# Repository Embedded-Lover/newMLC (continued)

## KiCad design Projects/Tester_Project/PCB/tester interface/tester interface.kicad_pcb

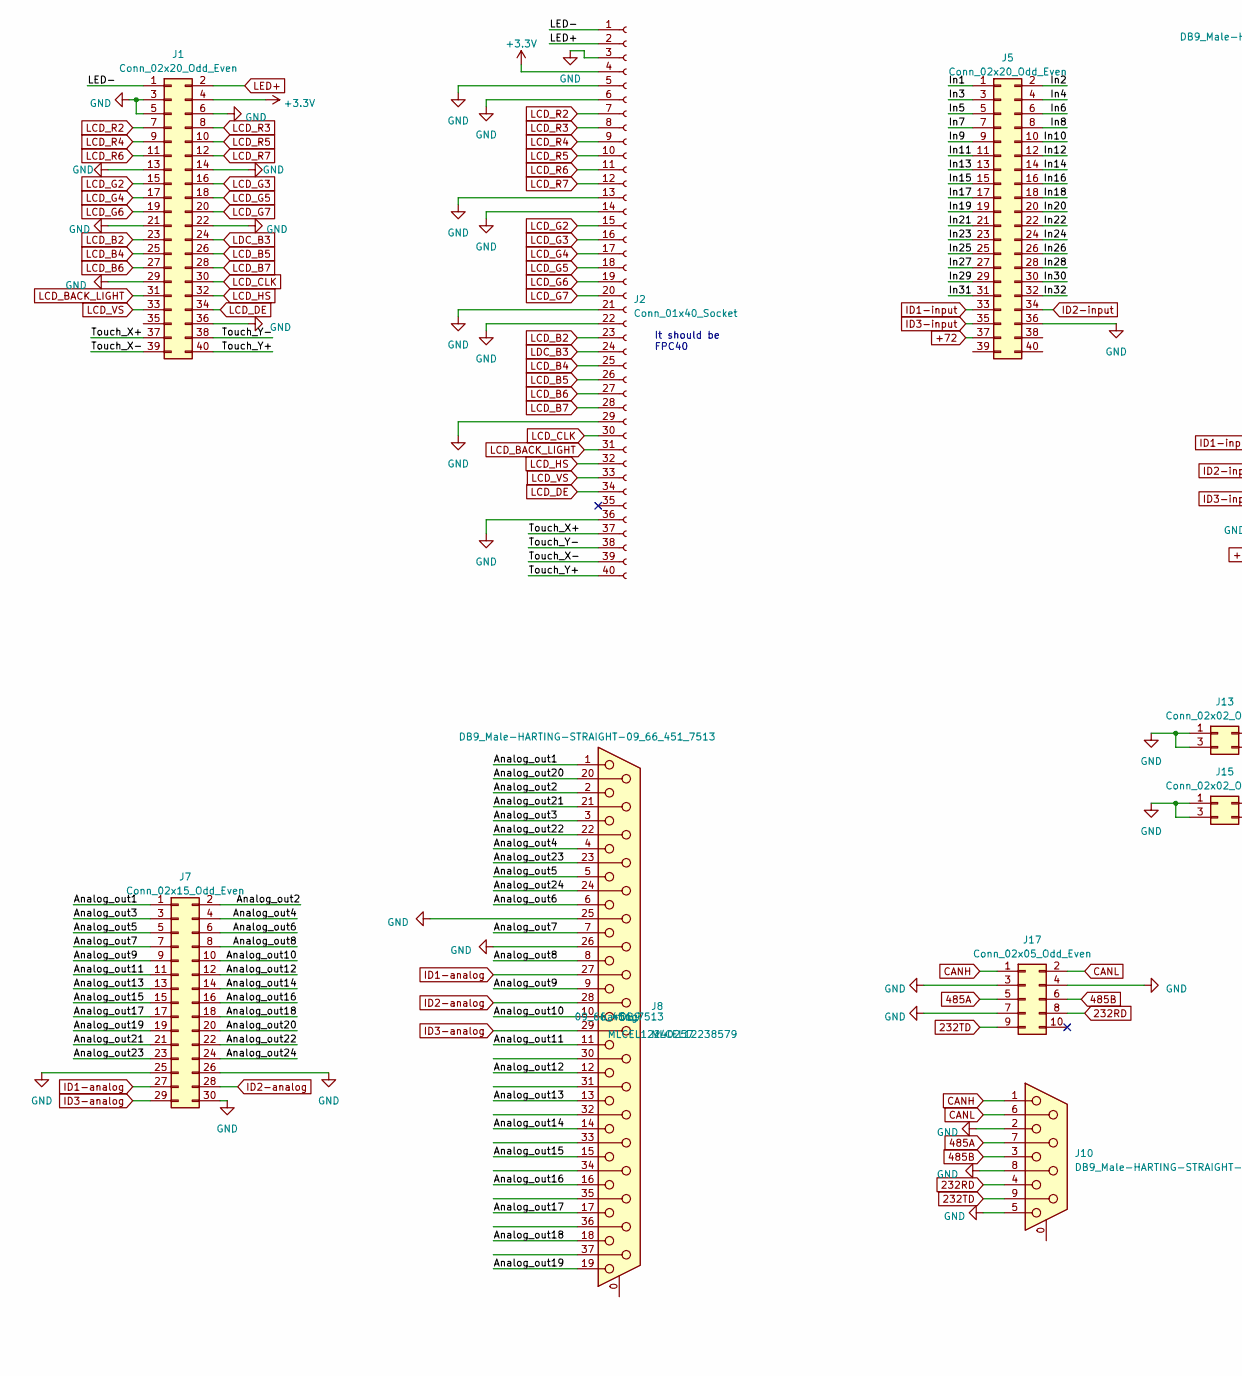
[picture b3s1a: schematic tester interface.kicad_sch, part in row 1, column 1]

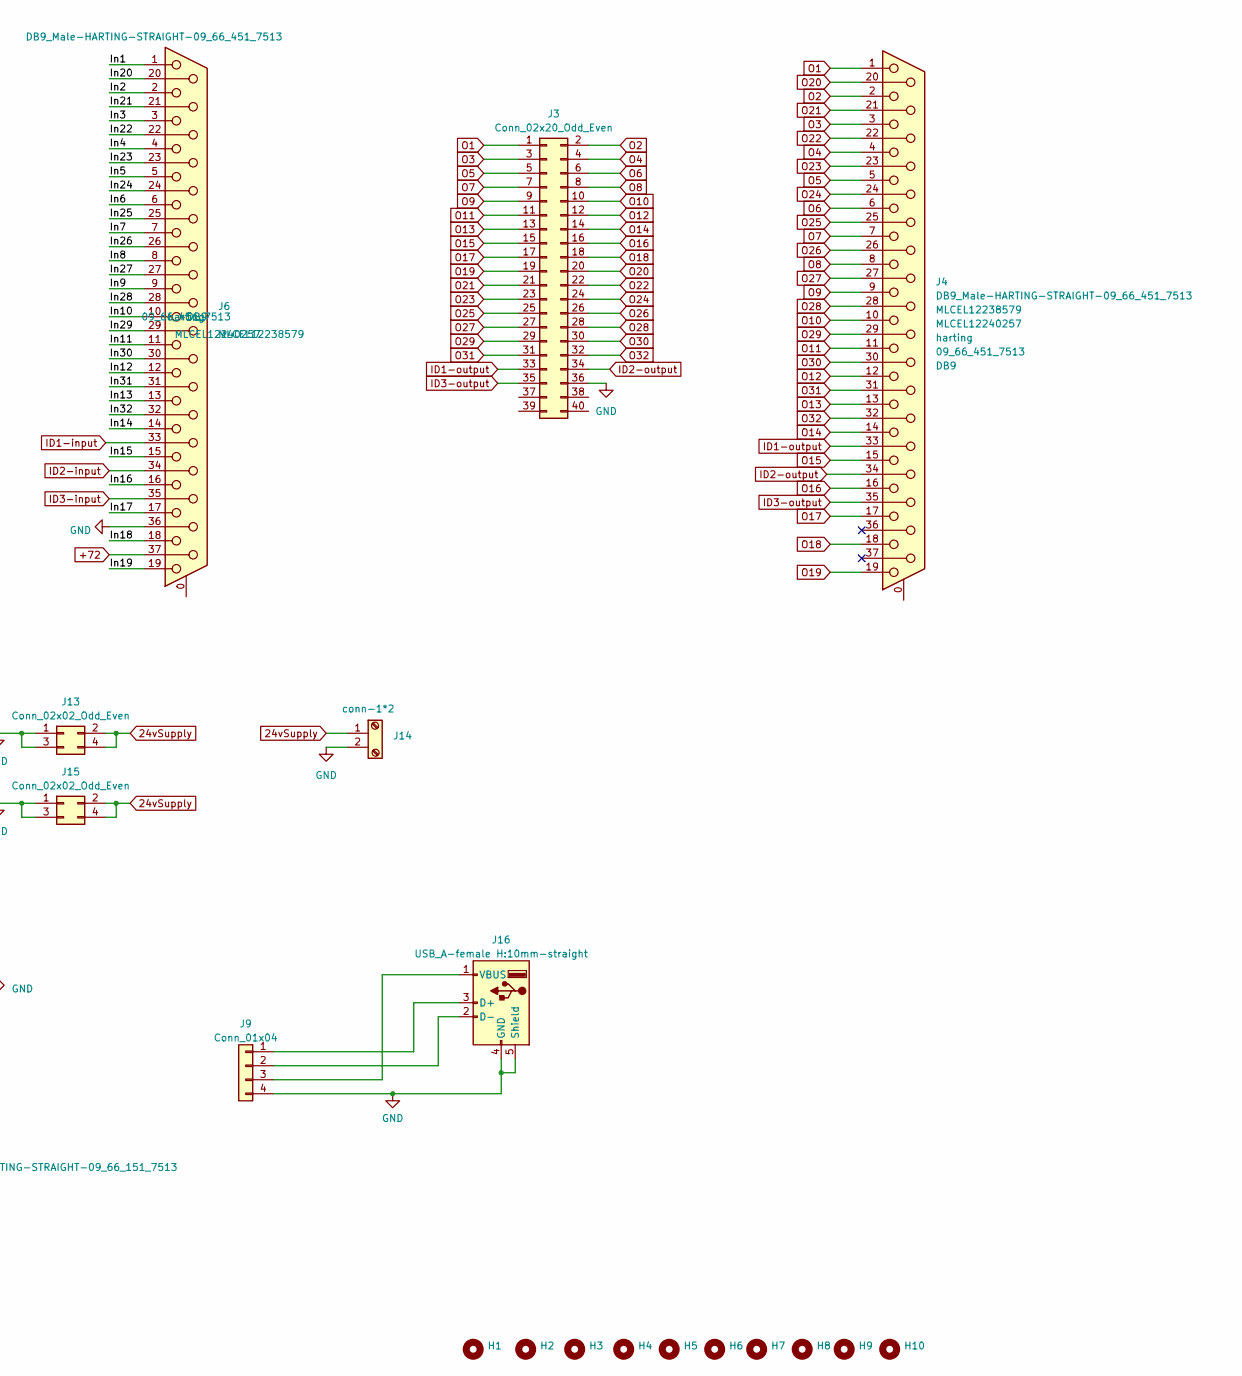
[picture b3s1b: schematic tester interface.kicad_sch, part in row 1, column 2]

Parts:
H1, H2, H3, H4, H5, H6, H7, H8, H9, H10: MountingHole; MountingHole_3.5mm_Pad_Via
J1, J3, J5: Conn_02x20_Odd_Even; PinSocket_2x20_P2.54mm_Vertical
J2: Conn_01x40_Socket; FPC-40way_P0.50mm_Horizontal
J4, J6, J8: DB9_Male-HARTING-STRAIGHT-09_66_451_7513; DSUB-37_Female_Vertical_P2.77x2.84mm_MountingHoles; MPN 09_66_451_7513
J7: Conn_02x15_Odd_Even; PinSocket_2x15_P2.54mm_Vertical
J9: Conn_01x04; PinSocket_1x04_P2.54mm_Vertical
J10: DB9_Male-HARTING-STRAIGHT-09_66_151_7513; DSUB-9_Female_Vertical_P2.77x2.84mm_MountingHoles; MPN 09_66_151_7513
J13, J15: Conn_02x02_Odd_Even; PinSocket_2x02_P2.54mm_Vertical
J14: -1*2-P5.08_straight_ThreadedFlange_MountHole; PhoenixContact_MCV_1,5_2-GF-3.81_1x02_P3.81mm_Vertical_Thre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; MPN 15EDGVM-3.81-02P-14-00A(H)
J16: USB_A-female H:10mm-straight; USB_A_Molex_105057_Vertical; MPN SOFNG
J17: Conn_02x05_Odd_Even; PinSocket_2x05_P2.54mm_Vertical

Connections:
24vSupply: J13.2, J13.4, J14.1, J15.2, J15.4
232RD: J10.4, J17.8
232TD: J10.9, J17.9
485A: J10.7, J17.5
485B: J10.3, J17.6
+3.3V: J1.4, J2.4
+72: J5.37, J6.37
/Analog_out1: J7.1, J8.1
/Analog_out2: J7.2, J8.2
/Analog_out3: J7.3, J8.3
/Analog_out4: J7.4, J8.4
/Analog_out5: J7.5, J8.5
/Analog_out6: J7.6, J8.6
/Analog_out7: J7.7, J8.7
/Analog_out8: J7.8, J8.8
/Analog_out9: J7.9, J8.9
/Analog_out10: J7.10, J8.10
/Analog_out11: J7.11, J8.11
/Analog_out12: J7.12, J8.12
/Analog_out13: J7.13, J8.13
/Analog_out14: J7.14, J8.14
/Analog_out15: J7.15, J8.15
/Analog_out16: J7.16, J8.16
/Analog_out17: J7.17, J8.17
/Analog_out18: J7.18, J8.18
/Analog_out19: J7.19, J8.19
/Analog_out20: J7.20, J8.20
/Analog_out21: J7.21, J8.21
/Analog_out22: J7.22, J8.22
/Analog_out23: J7.23, J8.23
/Analog_out24: J7.24, J8.24
/In1: J5.1, J6.1
/In2: J5.2, J6.2
/In3: J5.3, J6.3
/In4: J5.4, J6.4
/In5: J5.5, J6.5
/In6: J5.6, J6.6
/In7: J5.7, J6.7
/In8: J5.8, J6.8
/In9: J5.9, J6.9
/In10: J5.10, J6.10
/In11: J5.11, J6.11
/In12: J5.12, J6.12
/In13: J5.13, J6.13
/In14: J5.14, J6.14
/In15: J5.15, J6.15
/In16: J5.16, J6.16
/In17: J5.17, J6.17
/In18: J5.18, J6.18
/In19: J5.19, J6.19
/In20: J5.20, J6.20
/In21: J5.21, J6.21
/In22: J5.22, J6.22
/In23: J5.23, J6.23
/In24: J5.24, J6.24
/In25: J5.25, J6.25
/In26: J5.26, J6.26
/In27: J5.27, J6.27
/In28: J5.28, J6.28
/In29: J5.29, J6.29
/In30: J5.30, J6.30
/In31: J5.31, J6.31
/In32: J5.32, J6.32
/LED-: J1.1, J2.1
/Touch_X+: J1.37, J2.37
/Touch_X-: J1.39, J2.39
/Touch_Y+: J1.40, J2.40
/Touch_Y-: J1.38, J2.38
CANH: J10.1, J17.1
CANL: J10.6, J17.2
GND: J1.3, J1.5, J1.6, J1.13, J1.14, J1.21, J1.22, J1.29, J1.36, J2.3, J2.5, J2.6, J2.13, J2.14, J2.21, J2.22, J2.29, J2.36, J3.36, J5.36, J6.36, J7.25, J7.26, J7.30, J8.25, J8.26, J9.4, J10.2, J10.5, J10.8, J13.1, J13.3, J14.2, J15.1, J15.3, J16.4 (GND), J16.5 (Shield), J17.3, J17.4, J17.7
ID1-analog: J7.27, J8.27
ID1-input: J5.33, J6.33
ID1-output: J3.33, J4.33
ID2-analog: J7.28, J8.28
ID2-input: J5.34, J6.34
ID2-output: J3.34, J4.34
ID3-analog: J7.29, J8.29
ID3-input: J5.35, J6.35
ID3-output: J3.35, J4.35
LCD_B2: J1.23, J2.23
LCD_B4: J1.25, J2.25
LCD_B5: J1.26, J2.26
LCD_B6: J1.27, J2.27
LCD_B7: J1.28, J2.28
LCD_BACK_LIGHT: J1.31, J2.31
LCD_CLK: J1.30, J2.30
LCD_DE: J1.34, J2.34
LCD_G2: J1.15, J2.15
LCD_G3: J1.16, J2.16
LCD_G4: J1.17, J2.17
LCD_G5: J1.18, J2.18
LCD_G6: J1.19, J2.19
LCD_G7: J1.20, J2.20
LCD_HS: J1.32, J2.32
LCD_R2: J1.7, J2.7
LCD_R3: J1.8, J2.8
LCD_R4: J1.9, J2.9
LCD_R5: J1.10, J2.10
LCD_R6: J1.11, J2.11
LCD_R7: J1.12, J2.12
LCD_VS: J1.33, J2.33
LDC_B3: J1.24, J2.24
LED+: J1.2, J2.2
unnamed: J9.1, J16.3 (D+)
unnamed: J9.2, J16.2 (D-)
unnamed: J9.3, J16.1 (VBUS)
O1: J3.1, J4.1
O2: J3.2, J4.2
O3: J3.3, J4.3
O4: J3.4, J4.4
O5: J3.5, J4.5
O6: J3.6, J4.6
O7: J3.7, J4.7
O8: J3.8, J4.8
O9: J3.9, J4.9
O10: J3.10, J4.10
O11: J3.11, J4.11
O12: J3.12, J4.12
O13: J3.13, J4.13
O14: J3.14, J4.14
O15: J3.15, J4.15
O16: J3.16, J4.16
O17: J3.17, J4.17
O18: J3.18, J4.18
O19: J3.19, J4.19
O20: J3.20, J4.20
O21: J3.21, J4.21
O22: J3.22, J4.22
O23: J3.23, J4.23
O24: J3.24, J4.24
O25: J3.25, J4.25
O26: J3.26, J4.26
O27: J3.27, J4.27
O28: J3.28, J4.28
O29: J3.29, J4.29
O30: J3.30, J4.30
O31: J3.31, J4.31
O32: J3.32, J4.32

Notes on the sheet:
It should be FPC40

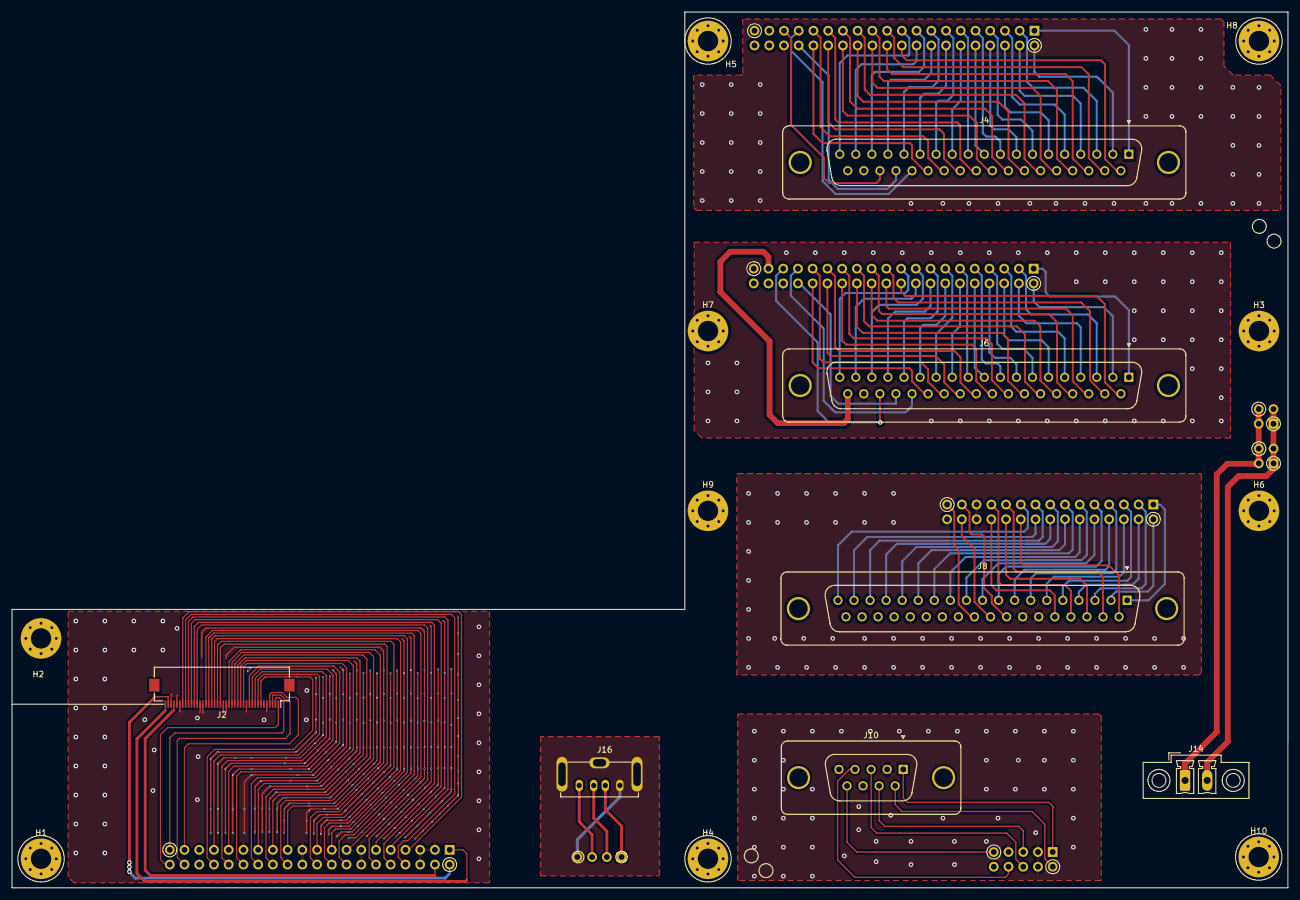
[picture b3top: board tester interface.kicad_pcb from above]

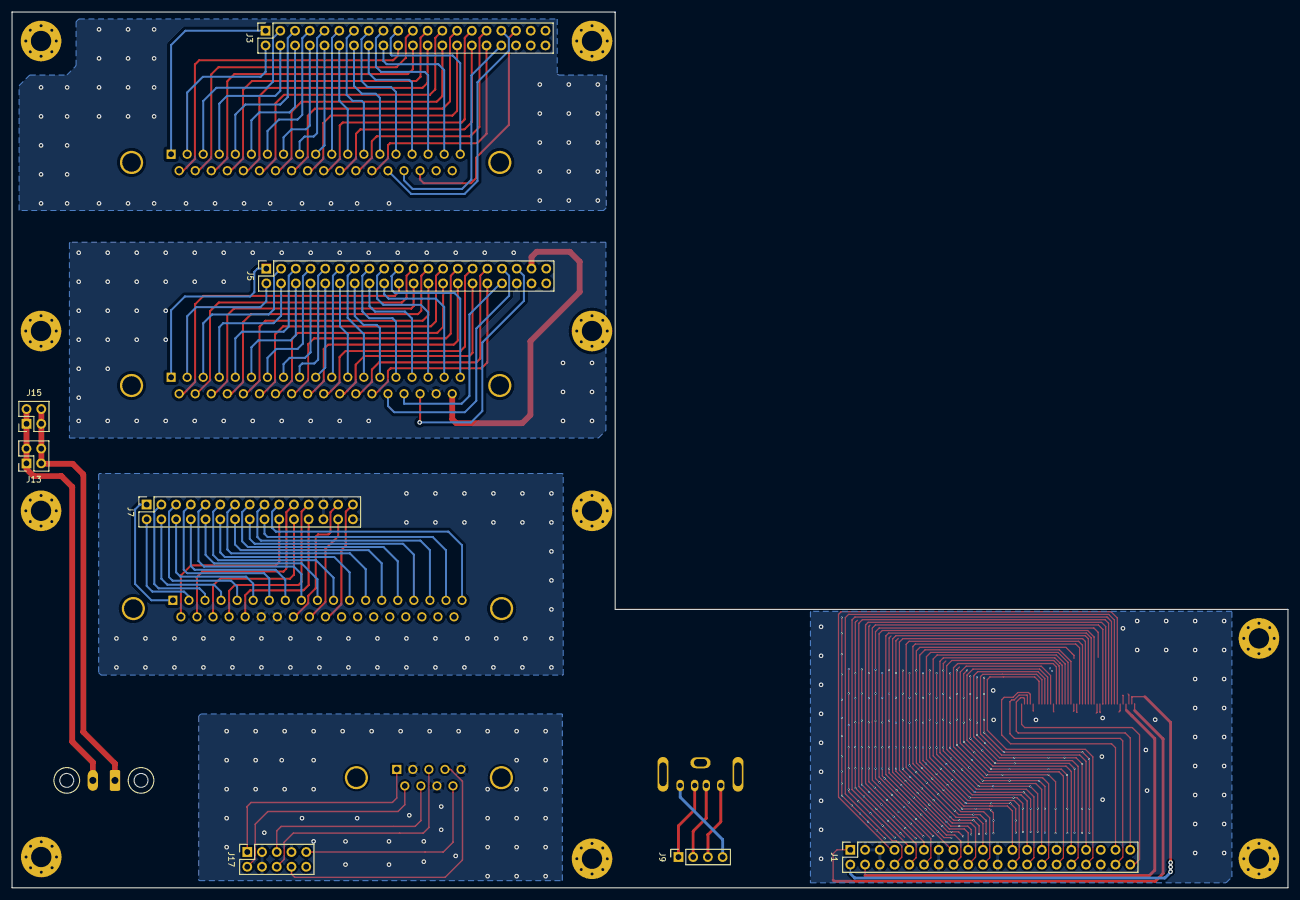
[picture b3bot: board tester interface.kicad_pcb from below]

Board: 2 copper layers, 220.0 x 151.0 mm, 25 parts (8 on the bottom side), 139 nets.
